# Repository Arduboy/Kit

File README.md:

# Arduboy Kit

This repository includes all of the files you need to build your own Arduboy Kit

## Important Notes

Arduboy Kit uses the "Alternate Wiring" pinout configuration. The pins necessary to match the production Arduboy FX are not available on the Pro-Micro module, and thus alternate assignments are made in software, at compile time using a custom board file. All code for the Arduboy Kit must be compiled for alternate wiring.

Solder jumpers are available on the back of the PCB, to switch to a standard wiring configuration, however this requires placing a PNP transistor along with a resistor. This modification is currently undocumented.

Additionally, Infrared LED has been placed instead of the Red led usually on Pin 9. An Infrared receiver has it's data pin instead of the Blue led usually on Pin 10.

## Eagle and Gerber Board Files

Use your favorite PCB board manufacturer to produce your own circuit boards. Files are contained within the Board Files folder

## Bill of Materials

List of required materials along with URL links to source the components. The links are for reference only, and are not endorsements of any particular seller. Purchase at your own discretion.

## Instructions

For instructions how to assemble the board are available within this repo:
- <a href="https://arduboy.github.io/Kit/Instructions.html">Web Instructions</a>
- <a href="https://arduboy.github.io/Kit/Instructions.pdf">Print Instructions</a>

A web utility for flashing all of the games to the Kit is within this repo:
- <a href="./index.html">Arduboy Kit Web Flasher</a>

and hosted at:
- <a href="https://arduboy.github.io/Kit">arduboy.github.io/Kit</a>

## 3d Printables

The step file for the Arduboy Kit and an example bottom clamshell case are available within the 3d Files folder.

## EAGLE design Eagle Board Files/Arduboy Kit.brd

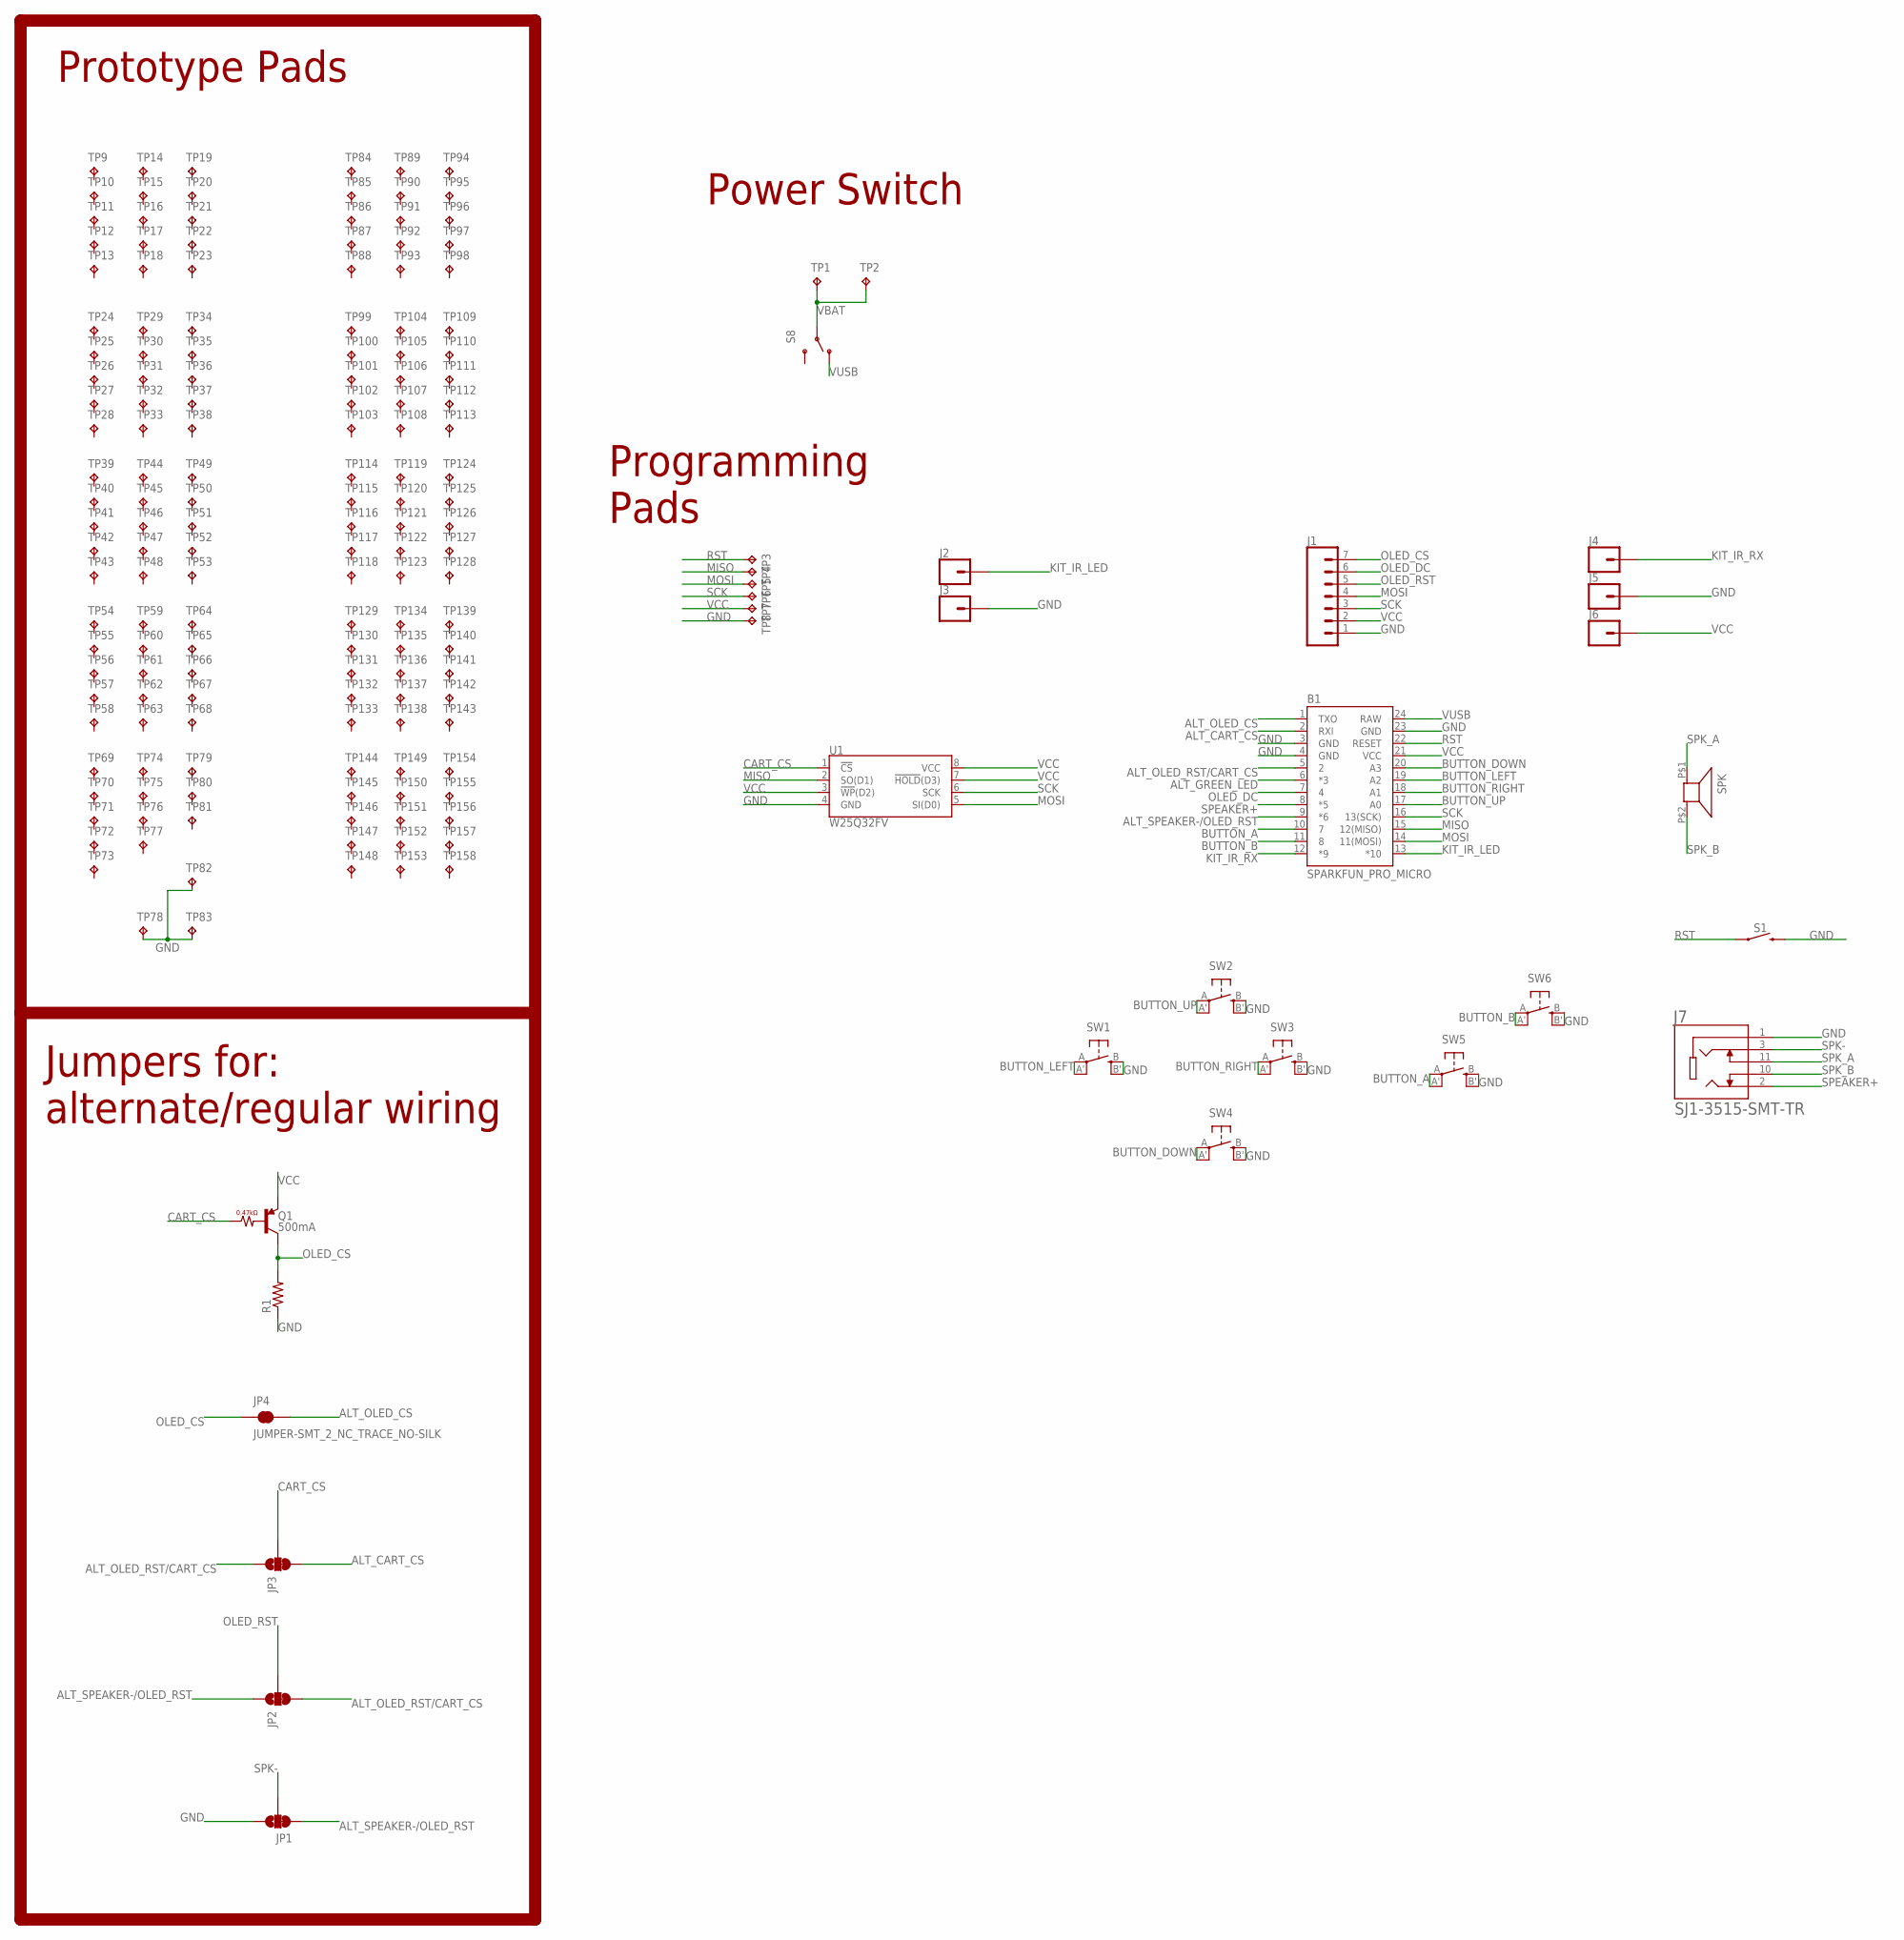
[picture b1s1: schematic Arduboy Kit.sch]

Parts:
B1: SPARKFUN_PRO_MICRO
J1: CONN_07NO_SILK; 1X07_NO_SILK
J2, J3, J4, J5, J6: CONN_01PAD; 1X01_SOLDER_PADS
J7: SJ1-3515-SMT-TR; CUI_SJ1-3515-SMT-TR
JP1, JP2, JP3: JUMPER-SMT_3_1-NC_TRACE_NO-SILK; SMT-JUMPER_3_1-NC_TRACE_NO-SILK
JP4: JUMPER-SMT_2_NC_TRACE_NO-SILK; SMT-JUMPER_2_NC_TRACE_NO-SILK
Q1: 500mA; SOT23-3
R1: R-US_R0805; R0805
S1: MOMENTARY-SWITCH-SPST-SMD-6.0X3.5MM; TACTILE_SWITCH_SMD_6.0X3.5MM
S8: SWITCH-SPDT-SMD-A; SWITCH-SPST-SMD-A
SPK: O_SPK_2_FLEX; O_SPK_FLEX
SW1, SW2, SW3, SW4, SW5, SW6: SPST_TACT-EVQQ2; EVQ-Q2
TP1, TP2, TP9, TP10, TP11, TP12, TP13, TP14, TP15, TP16, TP17, TP18, TP19, TP20, TP21, TP22, TP23, TP24, TP25, TP26, TP27, TP28, TP29, TP30, TP31, TP32, TP33, TP34, TP35, TP36, TP37, TP38, TP39, TP40, TP41, TP42, TP43, TP44, TP45, TP46, TP47, TP48, TP49, TP50, TP51, TP52, TP53, TP54, TP55, TP56, TP57, TP58, TP59, TP60, TP61, TP62, TP63, TP64, TP65, TP66, TP67, TP68, TP69, TP70, TP71, TP72, TP73, TP74, TP75, TP76, TP77, TP78, TP79, TP80, TP81, TP82, TP83, TP84, TP85, TP86, TP87, TP88, TP89, TP90, TP91, TP92, TP93, TP94, TP95, TP96, TP97, TP98, TP99, TP100, TP101, TP102, TP103, TP104, TP105, TP106, TP107, TP108, TP109, TP110, TP111, TP112, TP113, TP114, TP115, TP116, TP117, TP118, TP119, TP120, TP121, TP122, TP123, TP124, TP125, TP126, TP127, TP128, TP129, TP130, TP131, TP132, TP133, TP134, TP135, TP136, TP137, TP138, TP139, TP140, TP141, TP142, TP143, TP144, TP145, TP146, TP147, TP148, TP149, TP150, TP151, TP152, TP153, TP154, TP155, TP156, TP157, TP158: TPTP20SQ; TP20SQ
TP3, TP4, TP5, TP6, TP7, TP8: TPTP15SQ; TP15SQ
U1: W25Q32FV; SOIC-8

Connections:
ALT_CART_CS: B1.2 (RXI), JP3.3
ALT_GREEN_LED: B1.6 (*3)
ALT_OLED_CS: B1.1 (TXO), JP4.2
ALT_OLED_RST/CART_CS: B1.5 (2), JP2.3, JP3.1
ALT_SPEAKER-/OLED_RST: B1.9 (*6), JP1.3, JP2.1
BUTTON_A: B1.10 (7), SW5.A, SW5.A' (P1)
BUTTON_B: B1.11 (8), SW6.A, SW6.A' (P1)
BUTTON_DOWN: B1.20 (A3), SW4.A, SW4.A' (P1)
BUTTON_LEFT: B1.19 (A2), SW1.A, SW1.A' (P1)
BUTTON_RIGHT: B1.18 (A1), SW3.A, SW3.A' (P1)
BUTTON_UP: B1.17 (A0), SW2.A, SW2.A' (P1)
CART_CS: JP3.2, Q1.1 (B), U1.1 (!CS!)
GND: B1.3 (GND), B1.4 (GND), B1.23 (GND), J1.1, J3.1, J5.1, J7.1, JP1.1, R1.1, S1.2, SW1.B (S), SW1.B' (S1), SW2.B (S), SW2.B' (S1), SW3.B (S), SW3.B' (S1), SW4.B (S), SW4.B' (S1), SW5.B (S), SW5.B' (S1), SW6.B (S), SW6.B' (S1), TP8.TP, TP78.TP, TP82.TP, TP83.TP, U1.4 (GND)
KIT_IR_LED: B1.13 (*10), J2.1
KIT_IR_RX: B1.12 (*9), J4.1
MISO: B1.15 (12(MISO)), TP4.TP, U1.2 (SO(D1))
MOSI: B1.14 (11(MOSI)), J1.4, TP5.TP, U1.5 (SI(D0))
OLED_CS: J1.7, JP4.1, Q1.3 (C), R1.2
OLED_DC: B1.7 (4), J1.6
OLED_RST: J1.5, JP2.2
RST: B1.22 (RESET), S1.1, TP3.TP
SCK: B1.16 (13(SCK)), J1.3, TP6.TP, U1.6 (SCK)
SPEAKER+: B1.8 (*5), J7.2
SPK-: J7.3, JP1.2
SPK_A: J7.11, SPK.P$1 (1)
SPK_B: J7.10, SPK.P$2 (2)
VBAT: S8.2, TP1.TP, TP2.TP
VCC: B1.21 (VCC), J1.2, J6.1, Q1.2 (E), TP7.TP, U1.3 (!WP!(D2)), U1.7 (!HOLD!(D3)), U1.8 (VCC)
VUSB: B1.24 (RAW), S8.1 (O)

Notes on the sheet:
Jumpers for: alternate/regular wiring
Prototype Pads
Power Switch
Programming Pads

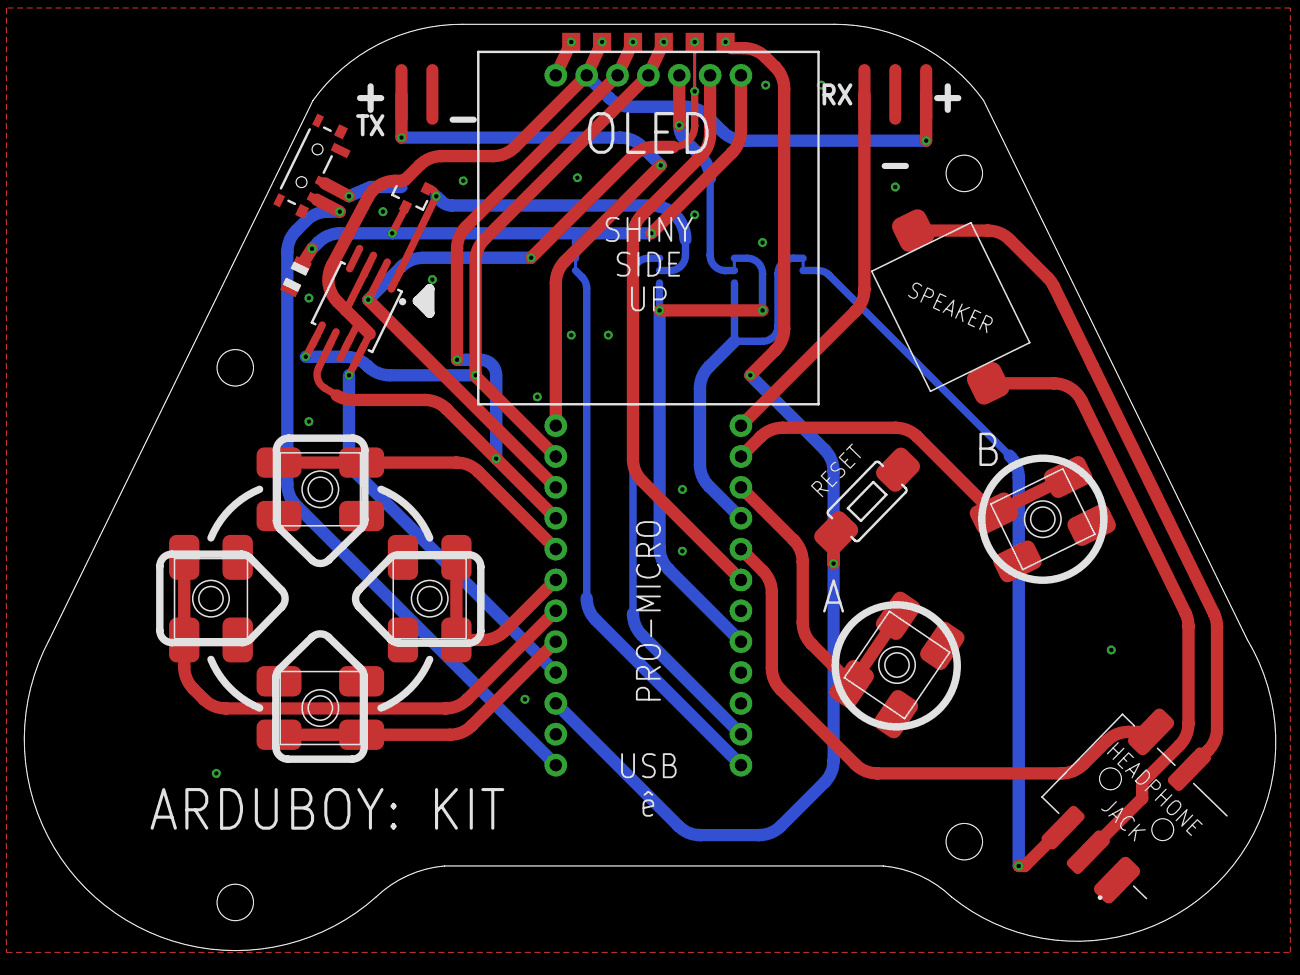
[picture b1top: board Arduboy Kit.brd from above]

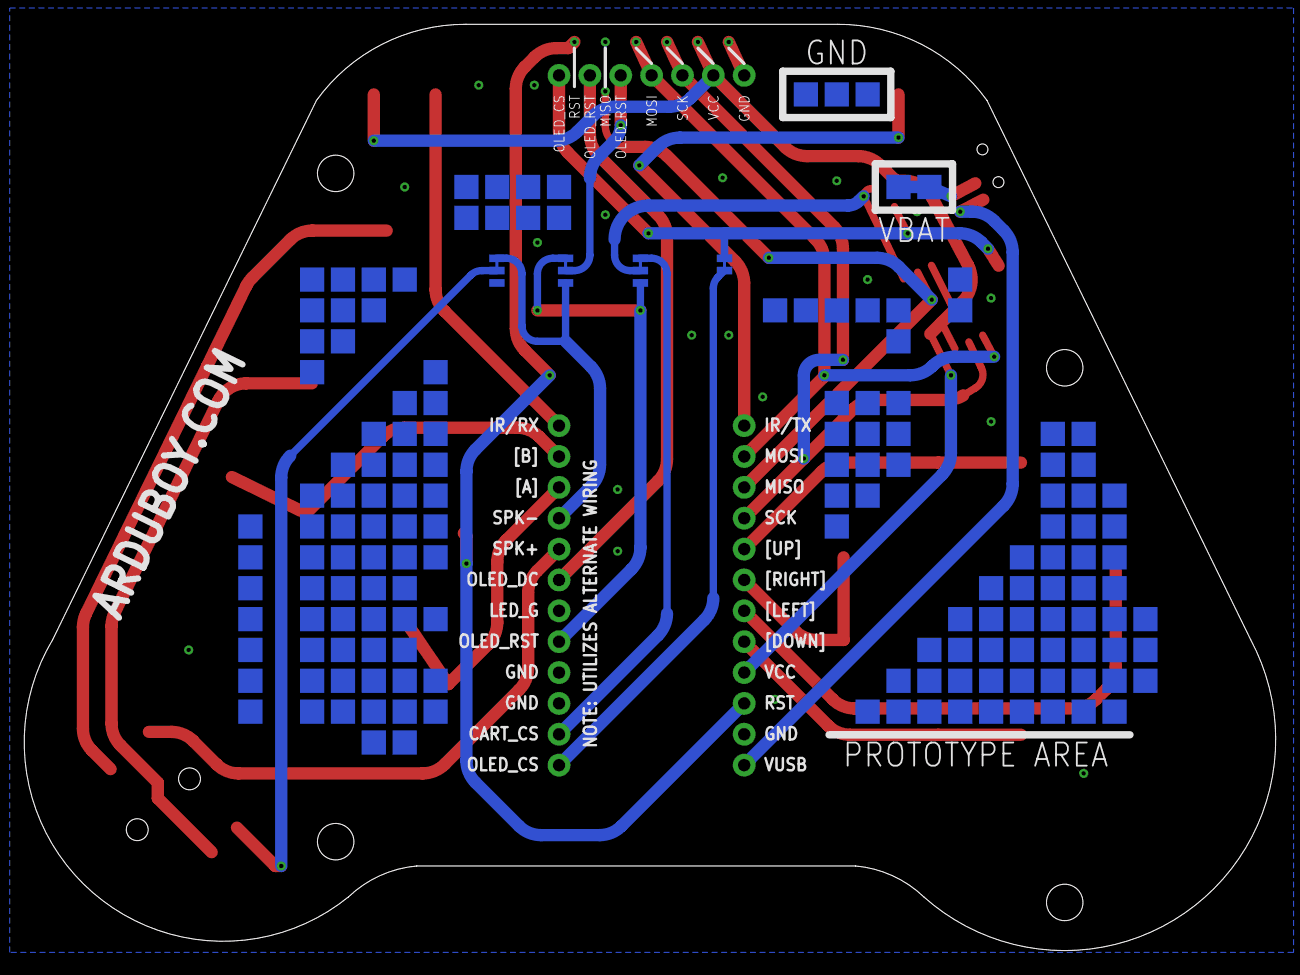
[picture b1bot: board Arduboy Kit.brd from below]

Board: 2 copper layers, 103.0 x 76.2 mm, 182 parts (156 on the bottom side), 28 nets.

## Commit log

2024-07-10 Adding Kit Instructions
2024-07-10 Rename Instructions
2024-07-10 Style Instructions
2024-07-10 Update Interface
2024-07-10 Cachebust
2024-07-29 Added board and 3d files
2024-07-29 Added Image
2024-07-29 Schematic

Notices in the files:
parts and their libraries:
SparkFun-Boards: Licensing: Creative Commons ShareAlike 4.0 International - https://creativecommons.org/licenses/by-sa/4.0
SparkFun-Electromechanical: Licensing: CC v3.0 Share-Alike You are welcome to use this library for commercial purposes.
